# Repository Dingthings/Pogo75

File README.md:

# Pogo75
Pogo Pin Based 75% keyboard with feature filled detachable numpad.

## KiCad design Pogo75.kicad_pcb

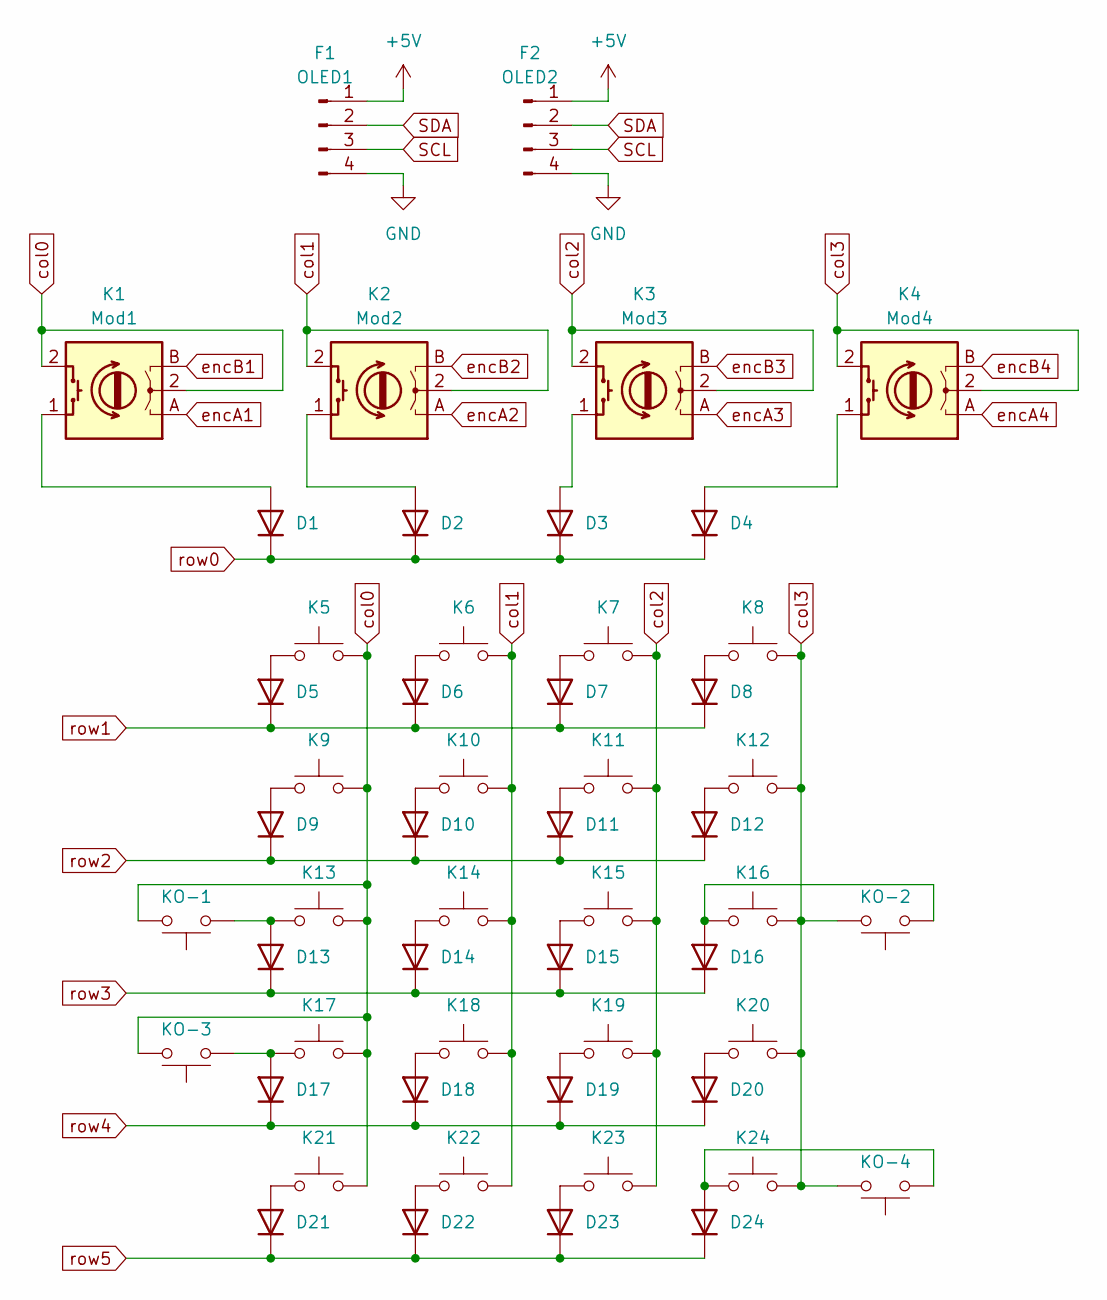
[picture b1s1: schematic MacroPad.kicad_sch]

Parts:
D1, D2, D3, D4, D5, D6, D7, D8, D9, D10, D11, D12, D13, D14, D15, D16, D17, D18, D19, D20, D21, D22, D23, D24: 1N4148W; D_SOD-123
F1: OLED1; PinHeader_1x04_P2.54mm_Vertical
F2: OLED2; PinHeader_1x04_P2.54mm_Vertical
K1: Mod1; SW_Hotswap_Kailh_MX_plated_1.00u_Enc
K2: Mod2; SW_Hotswap_Kailh_MX_plated_1.00u_Enc
K3: Mod3; SW_Hotswap_Kailh_MX_plated_1.00u_Enc
K4: Mod4; SW_Hotswap_Kailh_MX_plated_1.00u_Enc
K5: Num; SW_Hotswap_Kailh_MX_plated_1.00u
K6: /; SW_Hotswap_Kailh_MX_plated_1.00u
K7: *; SW_Hotswap_Kailh_MX_plated_1.00u
K8: -; SW_Hotswap_Kailh_MX_plated_1.00u
K9: 7; SW_Hotswap_Kailh_MX_plated_1.00u
K10: 8; SW_Hotswap_Kailh_MX_plated_1.00u
K11: 9; SW_Hotswap_Kailh_MX_plated_1.00u
K12, K16, K20, K23: SW_Push; SW_Hotswap_Kailh_MX_plated_1.00u
K13: 4; SW_Hotswap_Kailh_MX_plated_1.00u
K14: 5; SW_Hotswap_Kailh_MX_plated_1.00u
K15: 6; SW_Hotswap_Kailh_MX_plated_1.00u
K17: 1; SW_Hotswap_Kailh_MX_plated_1.00u
K18: 2; SW_Hotswap_Kailh_MX_plated_1.00u
K19: 3; SW_Hotswap_Kailh_MX_plated_1.00u
K21: 0; SW_Hotswap_Kailh_MX_plated_1.00u
K22: .; SW_Hotswap_Kailh_MX_plated_1.00u
K24: Enter; SW_Hotswap_Kailh_MX_plated_1.00u
KO-1, KO-2, KO-3, KO-4: 4; SW_Hotswap_Kailh_MX_plated_1.00u

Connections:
+5V: F1.1, F2.1; also elsewhere on the board
GND: F1.4, F2.4; also elsewhere on the board
unnamed: D1.2 (A), K1.1 (S1)
unnamed: D2.2 (A), K2.1 (S1)
unnamed: D3.2 (A), K3.1 (S1)
unnamed: D4.2 (A), K4.1 (S1)
unnamed: D5.2 (A), K5.1
unnamed: D6.2 (A), K6.1
unnamed: D7.2 (A), K7.1
unnamed: D8.2 (A), K8.1
unnamed: D9.2 (A), K9.1
unnamed: D10.2 (A), K10.1
unnamed: D11.2 (A), K11.1
unnamed: D12.2 (A), K12.1
unnamed: D13.2 (A), K13.1, KO-1.1
unnamed: D14.2 (A), K14.1
unnamed: D15.2 (A), K15.1
unnamed: D16.2 (A), K16.1, KO-2.1
unnamed: D17.2 (A), K17.1, KO-3.1
unnamed: D18.2 (A), K18.1
unnamed: D19.2 (A), K19.1
unnamed: D20.2 (A), K20.1
unnamed: D21.2 (A), K21.1
unnamed: D22.2 (A), K22.1
unnamed: D23.2 (A), K23.1
unnamed: D24.2 (A), K24.1, KO-4.1
SCL: F1.3, F2.3
SDA: F1.2, F2.2
col0: K1.2 (S2), K5.2, K9.2, K13.2, K17.2, K21.2, KO-1.2, KO-3.2
col1: K2.2 (C), K6.2, K10.2, K14.2, K18.2, K22.2
col2: K3.2 (S2), K7.2, K11.2, K15.2, K19.2, K23.2
col3: K4.2 (C), K8.2, K12.2, K16.2, K20.2, K24.2, KO-2.2, KO-4.2
encA1: K1.A
encA2: K2.A
encA3: K3.A
encA4: K4.A
encB1: K1.B
encB2: K2.B
encB3: K3.B
encB4: K4.B
row0: D1.1 (K), D2.1 (K), D3.1 (K), D4.1 (K)
row1: D5.1 (K), D6.1 (K), D7.1 (K), D8.1 (K)
row2: D9.1 (K), D10.1 (K), D11.1 (K), D12.1 (K)
row3: D13.1 (K), D14.1 (K), D15.1 (K), D16.1 (K)
row4: D17.1 (K), D18.1 (K), D19.1 (K), D20.1 (K)
row5: D21.1 (K), D22.1 (K), D23.1 (K), D24.1 (K)

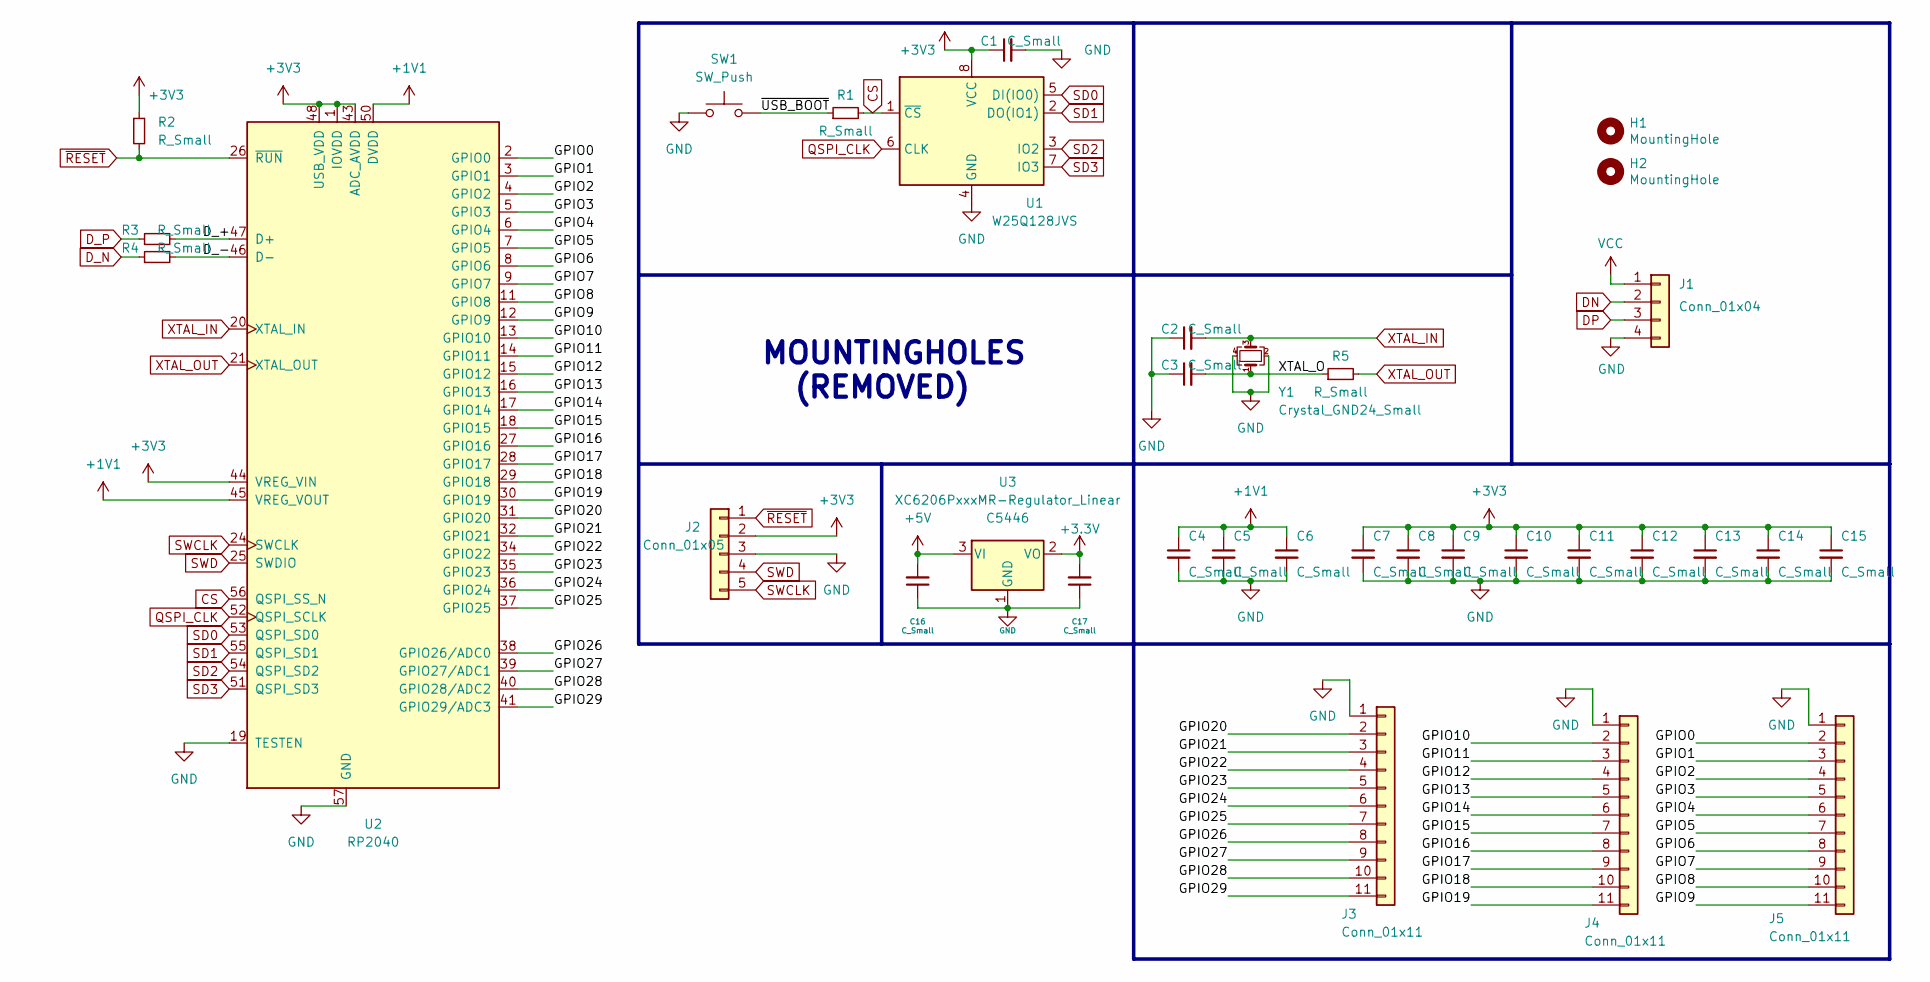
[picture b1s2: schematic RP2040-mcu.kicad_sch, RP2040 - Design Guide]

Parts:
C1, C5, C6, C9, C10, C11, C12, C13, C14, C15: C_Small; C_0402_1005Metric; LCSC C1525
C2, C3: C_Small; C_0402_1005Metric; LCSC C1555
C4, C8, C16, C17: C_Small; C_0402_1005Metric; LCSC C52923
C7: C_Small; C_0402_1005Metric; LCSC C15525
H1: MountingHole; Unified-Daughterboard-Logo.pretty
H2: MountingHole; Unified-Daughterboard-Name.pretty
J1: Conn_01x04; JST-SR-4; Manufacturer Part No SM04B-SRSS-TB(LF)(SN); LCSC Part No C160404
J2: Conn_01x05; PinSocket_1x05_P2.54mm_Vertical
J3, J4, J5: Conn_01x11; PinSocket_1x11_P2.54mm_Vertical
R1, R2, R5: R_Small; R_0402_1005Metric; LCSC C11702
R3, R4: R_Small; R_0603_1608Metric; LCSC C25190
SW1: SW_Push; PinSocket_1x02_P2.54mm_Vertical
U1: W25Q128JVS; SOIC-8_5.23x5.23mm_P1.27mm; LCSC C131025
U2: RP2040; RP2040-QFN-56; LCSC C2040
U3: XC6206PxxxMR-Regulator_Linear; SOT-23; LCSC C5446
Y1: Crystal_GND24_Small; Crystal_SMD_3225-4Pin_3.2x2.5mm; LCSC C9002

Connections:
+1V1: C4.1, C5.1, C6.1, U2.23 (DVDD), U2.45 (VREG_VOUT), U2.50 (DVDD)
+3.3V: C17.2, U3.2 (VO)
+3V3: C1.1, C7.1, C8.1, C9.1, C10.1, C11.1, C12.1, C13.1, C14.1, C15.1, J2.2, R2.1, U1.8 (VCC), U2.1 (IOVDD), U2.10 (IOVDD), U2.22 (IOVDD), U2.33 (IOVDD), U2.42 (IOVDD), U2.43 (ADC_AVDD), U2.44 (VREG_VIN), U2.48 (USB_VDD), U2.49 (IOVDD)
+5V: C16.2, U3.3 (VI); also elsewhere on the board
/RP2040/D_+: R3.2, U2.47 (D+)
/RP2040/D_-: R4.2, U2.46 (D-)
/RP2040/GPIO0: J5.2, U2.2 (GPIO0)
/RP2040/GPIO1: J5.3, U2.3 (GPIO1)
/RP2040/GPIO2: J5.4, U2.4 (GPIO2)
/RP2040/GPIO3: J5.5, U2.5 (GPIO3)
/RP2040/GPIO4: J5.6, U2.6 (GPIO4)
/RP2040/GPIO5: J5.7, U2.7 (GPIO5)
/RP2040/GPIO6: J5.8, U2.8 (GPIO6)
/RP2040/GPIO7: J5.9, U2.9 (GPIO7)
/RP2040/GPIO8: J5.10, U2.11 (GPIO8)
/RP2040/GPIO9: J5.11, U2.12 (GPIO9)
/RP2040/GPIO10: J4.2, U2.13 (GPIO10)
/RP2040/GPIO11: J4.3, U2.14 (GPIO11)
/RP2040/GPIO12: J4.4, U2.15 (GPIO12)
/RP2040/GPIO13: J4.5, U2.16 (GPIO13)
/RP2040/GPIO14: J4.6, U2.17 (GPIO14)
/RP2040/GPIO15: J4.7, U2.18 (GPIO15)
/RP2040/GPIO16: J4.8, U2.27 (GPIO16)
/RP2040/GPIO17: J4.9, U2.28 (GPIO17)
/RP2040/GPIO18: J4.10, U2.29 (GPIO18)
/RP2040/GPIO19: J4.11, U2.30 (GPIO19)
/RP2040/GPIO20: J3.2, U2.31 (GPIO20)
/RP2040/GPIO21: J3.3, U2.32 (GPIO21)
/RP2040/GPIO22: J3.4, U2.34 (GPIO22)
/RP2040/GPIO23: J3.5, U2.35 (GPIO23)
/RP2040/GPIO24: J3.6, U2.36 (GPIO24)
/RP2040/GPIO25: J3.7, U2.37 (GPIO25)
/RP2040/GPIO26: J3.8, U2.38 (GPIO26/ADC0)
/RP2040/GPIO27: J3.9, U2.39 (GPIO27/ADC1)
/RP2040/GPIO28: J3.10, U2.40 (GPIO28/ADC2)
/RP2040/GPIO29: J3.11, U2.41 (GPIO29/ADC3)
/RP2040/XTAL_O: C3.2, R5.1, Y1.1
/RP2040/~USB_BOOT: R1.1, SW1.2
CS: R1.2, U1.1 (~CS), U2.56 (QSPI_SS_N)
D_N: R4.1
D_P: R3.1
GND: C1.2, C2.1, C3.1, C4.2, C5.2, C6.2, C7.2, C8.2, C9.2, C10.2, C11.2, C12.2, C13.2, C14.2, C15.2, C16.1, C17.1, J1.4, J2.3, J3.1, J4.1, J5.1, SW1.1, U1.4 (GND), U2.19 (TESTEN), U2.57 (GND), U3.1 (GND), Y1.2, Y1.4; also elsewhere on the board
QSPI_CLK: U1.6 (CLK), U2.52 (QSPI_SCLK)
SD0: U1.5 (DI(IO0)), U2.53 (QSPI_SD0)
SD1: U1.2 (DO(IO1)), U2.55 (QSPI_SD1)
SD2: U1.3 (IO2), U2.54 (QSPI_SD2)
SD3: U1.7 (IO3), U2.51 (QSPI_SD3)
SWCLK: J2.5, U2.24 (SWCLK)
SWD: J2.4, U2.25 (SWDIO)
XTAL_IN: C2.2, U2.20 (XTAL_IN), Y1.3
XTAL_OUT: R5.2, U2.21 (XTAL_OUT)
~RESET: J2.1, R2.2, U2.26 (~RUN)

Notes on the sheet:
MOUNTINGHOLES (REMOVED)

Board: 2 copper layers, 85 parts (55 on the bottom side), 86 nets, no tracks yet.

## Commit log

2023-01-15 Created KiCad Project
    Hopefully this one will go to production
2023-01-15 Added submodules, libraries
2023-01-16 Configured custom footprint
2023-01-16 Modified directories
    Removed extraneous RP2040-guide materials
2023-01-16 Assigned footprints
    Macropad + RP2040
2023-01-17 Modified enc footprint
